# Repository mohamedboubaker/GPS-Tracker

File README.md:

- Detailed Design + Doxygen Code Documentation has been moved to <a href="https://embeddedprojects101.com/stm32-and-sim808-gps-tracker-with-a-custom-pcb/">embeddedprojects101.com/</a> 

- Contact Information: <a href="https://www.linkedin.com/in/mohamed-boubaker/">Linkedin</a>

*Produced PCB board*

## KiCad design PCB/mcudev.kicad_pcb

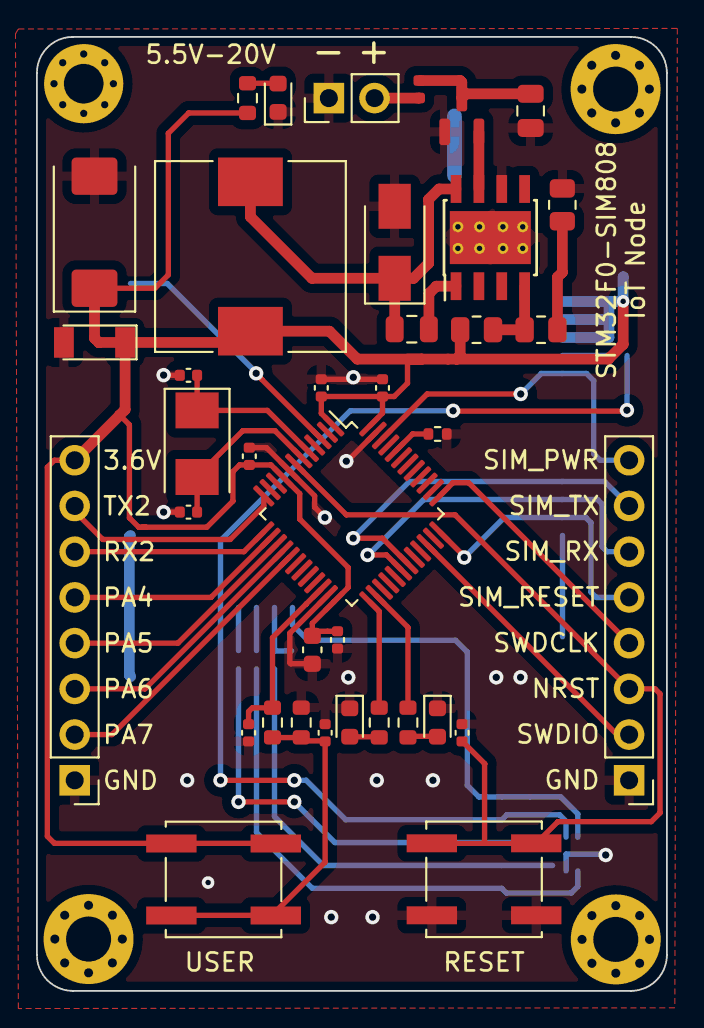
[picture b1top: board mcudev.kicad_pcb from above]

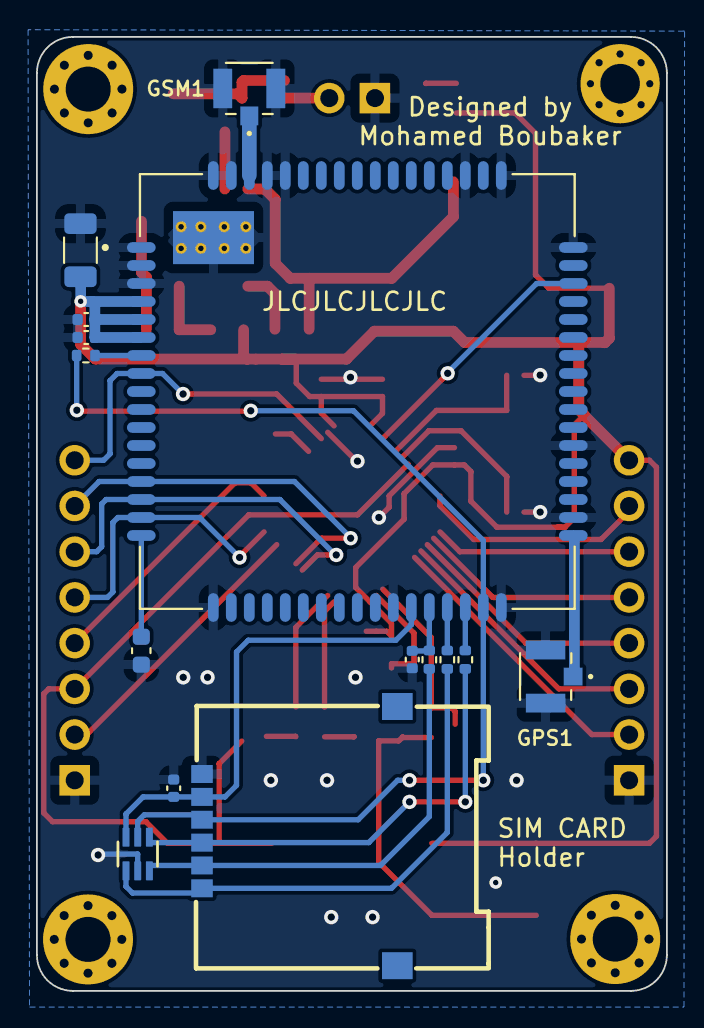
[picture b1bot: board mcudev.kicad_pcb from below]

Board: 2 copper layers, 35.0 x 53.0 mm, 57 parts (15 on the bottom side), 45 nets.

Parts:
C1: 220u; CP_EIA-7343-15_Kemet-W
D1: LED1; LED_0603_1608Metric
D2: LED2; LED_0603_1608Metric
D3: B340; D_SMA
D4: PWR Status; LED_0603_1608Metric
D5: D_Zener; LL-34
F1: Fuse 2.5A; Fuse_0402_1005Metric
GPS1: U.FL-R-SMT(10); HRS_U.FL-R-SMT(10)
GSM1: U.FL-R-SMT(10); HRS_U.FL-R-SMT(10)
H1, H2, H4: MountingHole; MountingHole_2.5mm_Pad_Via
H3: MountingHole; MountingHole_2.2mm_M2_Pad_Via
J1: Right Header Pins; PinHeader_1x08_P2.54mm_Vertical
J2: Left Header Pins; PinHeader_1x08_P2.54mm_Vertical
J4: 5V-20V; PinHeader_1x02_P2.54mm_Vertical
L1: 15uH; L_10.4x10.4_H4.8
P1: SMO-1512; SIM-SMD_SMO-1512
Q1: AO3407; SOT-23
R1, R2, R8: 1k5; R_0603_1608Metric
R3: 10K; R_0402_1005Metric
R4, R5, R12: R22; R_0402_1005Metric
R6: 1K; R_0603_1608Metric
R7: 100K; R_0603_1608Metric
R9: 8k2; R_0805_2012Metric
R10: 1k5; R_0805_2012Metric
R11: 2k7; R_0805_2012Metric
R13: 4k7; R_0402_1005Metric
STM32F30: STM32F030C8Tx; LQFP-48_7x7mm_P0.5mm
SW1, SW2: SW_Push; SW_Push_1P1T_NO_CK_KSC6xxJ
U1, U17: 4u7; C_0603_1608Metric
U2, U3, U4, U5, U6, U12: 100n; C_0402_1005Metric
U7: 8MHz; Crystal_SMD_5032-2Pin_5.0x3.2mm
U8, U9: 30p; C_0402_1005Metric
U11, U22: 10p; C_0402_1005Metric
U13: 10n; C_0805_2012Metric
U14: TPS5430DDA; TI_SO-PowerPAD-8_ThermalVias
U15: 10u; C_0805_2012Metric
U16: SIM808; XCVR_SIM808
U18: 1u; C_0402_1005Metric
U19: 22p; C_0402_1005Metric
U20: 100u; C_1206_3216Metric
U21: 33p; C_0402_1005Metric
U23: SMF05CT1G; SOT65P210X110-6N

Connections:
+3.3V: C1.1, D5.1 (K), J2.8, L1.2, R8.1, R9.1, STM32F30.1 (VDD), STM32F30.9 (VDDA), STM32F30.24 (VDD), STM32F30.48 (VDD), SW2.2, U1.1, U2.1, U3.1, U4.1, U5.1, U16.4 (VBAT), U16.5 (VBAT), U16.6 (VBAT), U20.1, U21.1, U22.1
+12V: F1.1, J4.2
/BOOT0: R3.2, STM32F30.44 (BOOT0)
/HSE_IN: STM32F30.5 (PF0), U7.1, U8.1
/HSE_OUT: STM32F30.6 (PF1), U7.2, U9.1
GND: C1.2, D1.1 (K), D2.1 (K), D3.2 (A), D4.1 (K), D5.2 (A), GPS1.2, GPS1.3, GSM1.2, GSM1.3, J1.1, J2.1, J4.1, P1.C5 (GND), Q1.1 (G), R3.1, R7.2, R11.2, STM32F30.8 (VSSA), STM32F30.23 (VSS), STM32F30.47 (VSS), SW1.2, U1.2, U2.2, U3.2, U4.2, U5.2, U6.2, U8.2, U9.2, U11.2, U12.2, U14.6 (GND), U14.9 (GNDPAD), U15.2, U16.1 (GND), U16.2 (GND), U16.3 (GND), U16.18 (GND), U16.28 (GND), U16.34 (GND), U16.36 (GND), U16.40 (GND), U16.51 (GND), U16.52 (GND), U16.54 (GND), U16.64 (GND), U16.65 (GND), U16.67 (GND), U16.68 (GND), U17.2, U18.1, U19.2, U20.2, U21.2, U22.2, U23.2
GPS_ANT: GPS1.1, U16.35 (GPS_ANT)
GSM_ANT: GSM1.1, U16.66 (GSM_ANT)
LED1: R2.1, STM32F30.25 (PB12)
LED2: R1.1, STM32F30.26 (PB13)
NRST: J1.3, STM32F30.7 (NRST), SW1.1, U6.1
unnamed: D1.2 (A), R1.2
unnamed: D2.2 (A), R2.2
unnamed: D3.1 (K), L1.1, U13.2, U14.8 (PH)
unnamed: D4.2 (A), R8.2
unnamed: F1.2, Q1.3 (D), U15.1
unnamed: P1.C2 (RST), R4.2, U23.4
unnamed: P1.C3 (CLK), R5.2, U23.1
unnamed: P1.C7 (DATA), R12.2, U23.3
unnamed: Q1.2 (S), U14.7 (VIN)
unnamed: R6.1, STM32F30.22 (PB11), U12.1
unnamed: R6.2, R7.1, SW2.1, U11.1
unnamed: R10.2, R11.1
unnamed: R13.1, U16.7 (VDD_EXT)
unnamed: U13.1, U14.1 (BOOT)
unnamed: U16.17 (VRTC), U17.1
PA4: J2.5, STM32F30.14 (PA4)
PA5/SPI1_CLK: J2.4, STM32F30.15 (PA5)
PA6/SPI1_MISO: J2.3, STM32F30.16 (PA6)
PA7/SPI1_MOSI: J2.2, STM32F30.17 (PA7)
SIM_CLK: R5.1, U16.31 (SIM_CLK)
SIM_DATA: R12.1, U16.30 (SIM_DATA), U19.1
SIM_DET: P1.C6 (VPP), R13.2, U16.33 (SIM_DET), U23.5
SIM_PWRKEY: J1.8, STM32F30.46 (PB9), U16.8 (PWRKEY)
SIM_RESET: J1.5, STM32F30.36 (PF7), U16.16 (~RESET)
SIM_RST: R4.1, U16.32 (SIM_RST)
SIM_RX: J1.6, STM32F30.30 (PA9), U16.15 (RXD)
SIM_TX: J1.7, STM32F30.31 (PA10), U16.14 (TXD)
SIM_VDD: P1.C1 (VDD), U16.29 (SIM_VDD), U18.2, U23.6
STATUS: STM32F30.3 (PC14), U16.49 (STATUS)
SWDCLK: J1.4, STM32F30.37 (PA14)
SWDIO: J1.2, STM32F30.34 (PA13)
USART2_RX: J2.6, STM32F30.13 (PA3)
USART2_TX: J2.7, STM32F30.12 (PA2)
feedback: R9.2, R10.1, U14.4 (VSENSE)

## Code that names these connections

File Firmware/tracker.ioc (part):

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Mcu.Name=STM32F051R8Tx
Mcu.Package=LQFP64
Mcu.UserName=STM32F051R8Tx
PA10.Mode=Asynchronous
PA10.Signal=USART1_RX
PA2.Mode=Asynchronous
PA2.Signal=USART2_TX
PA3.Mode=Asynchronous
PA3.Signal=USART2_RX
PA9.Mode=Asynchronous
PA9.Signal=USART1_TX
PB9.GPIOParameters=GPIO_PuPd,GPIO_ModeDefaultOutputPP
PB9.GPIO_ModeDefaultOutputPP=GPIO_MODE_OUTPUT_OD
PB9.GPIO_PuPd=GPIO_NOPULL
PB9.Signal=GPIO_Output
PC14-OSC32_IN.Signal=GPIO_Input
PC8.Signal=GPIO_Output
PC9.Signal=GPIO_Output
PF0-OSC_IN.Mode=HSE-External-Oscillator
PF0-OSC_IN.Signal=RCC_OSC_IN
PF1-OSC_OUT.Mode=HSE-External-Oscillator
PF1-OSC_OUT.Signal=RCC_OSC_OUT
PF7.GPIOParameters=GPIO_PuPd,GPIO_ModeDefaultOutputPP
PF7.GPIO_ModeDefaultOutputPP=GPIO_MODE_OUTPUT_OD
PF7.GPIO_PuPd=GPIO_NOPULL
PF7.Signal=GPIO_Output
RCC.SYSCLKFreq_VALUE=8000000
RCC.SYSCLKSource=RCC_SYSCLKSOURCE_HSE
board=custom

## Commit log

2022-12-23 Commit 1
2022-12-23 added code
2022-12-23 added todo and backlog
2022-12-23 added pcb image
2022-12-23 Pictures
2022-12-25 removd media
2022-12-25 backlog adjusted
2022-12-28 removed todo list
2022-12-28 removed backlog
2022-12-29 add doxygen comments
2023-01-01 Added KiCad Project
2023-01-04 changed sim_init, issue #23
2023-01-06 implementation
2023-01-15 added keil
2023-01-16 issue #27
2023-01-16 fixed indent
2023-01-16 issue #9
2023-01-16 added Media
2023-01-22 seperated functions in different files
2023-01-23 Pictures folder renamed
2023-01-25 replaced sim_tcp_send with open_tcp_connection, send_tcp_data and close_tcp_connection
2023-01-25 removed unnecesssary files
2023-01-25 removed unnecessary files
2023-01-25 Implementing matt publish
2023-01-27 added AES files
2023-01-27 changed dcoumentation
2023-01-27 added doxygen documentation html files
2023-01-27 removed PCB
2023-01-27 deleted all files except doxygen pages
2023-01-27 removed doxygen html
2023-01-27 added doxygen files
2023-01-27 cleaned main.c
2023-01-29 updated the subscriber script
2023-01-30 issue #32 create a universal function to interact with the module
2023-01-31 updated readme: circuit design section
2023-02-01 issue #32
2023-02-05 upated readme: circuit design section
2023-02-06 issue #11 added encryption code
2023-02-06 issue #11 modified encryption code
2023-02-06 issue #16 documentation
2023-02-07 issue #19 changing publish_mqtt_data()
2023-02-07 Functional version V1.0
2023-02-07 Picture
2023-02-10 Documentation improvement
2023-02-11 Added Function Call graps
2023-02-11 Added function call graphs
2023-03-07 added AES section
2023-03-07 added AES implementation section
2023-09-11 Update README.md
    updated SEO keywords
2023-10-05 moved documentation to embeddedprojects101.com
